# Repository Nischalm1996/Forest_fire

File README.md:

# Forest_fire

## BASE STATION
| NAME     | Pin |
|----------|-----|
| IO0_LORA | D2  |
| RX_GSM   | D3  |
| TX_GSM   | D4  |
| OK       | D5  |
| LEFT     | D6  |
| RIGHT    | D7  |
| BACK     | D8  |
| RST_LORA | D9  |
| SS_LORA  | D10 |
| MOSI     | D11 |
| MISO     | D12 |
| SCK      | D13 |

### MODULES USED
- LORA RA02--d
- GSM SIM 800L--d
- NAVIGATION MODULE --d
- DISPLAY I2C 16*2 --d https://github.com/VaSe7u/LiquidMenu

## NODE_DEVICE
| NAME     | Pin |
|----------|-----|
|   DHT11  | D5  |
| MQ2D0    | D6  |
| PIR      | D7  |
| IO0_LORA | D8  |
| RST_LORA | D9  |
| SS_LORA  | D10 |

### MODULES USED
- MQ2 -- d
- PIR --d
- DHT11-- d
- GPS --d
- LORA RA02 --d

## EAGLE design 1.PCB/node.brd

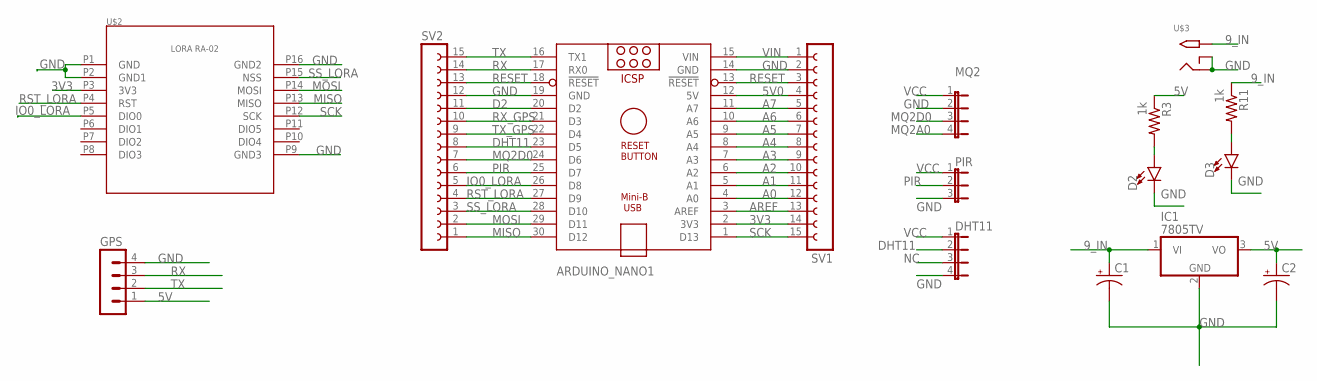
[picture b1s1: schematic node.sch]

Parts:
ARDUINO_NANO1: ARDUINO_NANO
C1, C2: CPOL-USE3.5-8; E3,5-8
D2, D3: LED3MM; LED_3MM
DHT11: JP4E; JP4
GPS: MA04-1
IC1: 7805TV; TO220V
MQ2: JP4E; JP4
PIR: JP2E; JP2
R3, R11: 1k; M0805
SV1, SV2: FE15-1; FE15
U$2: LORA_RA-02; RA-02
U$3: 2.1MMJACKTHM; PJ-102A

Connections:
3V3: ARDUINO_NANO1.2 (3V3), SV1.14, U$2.P3 (3V3)
5V: C2.+, GPS.1, IC1.3 (VO), R3.1
5V0: ARDUINO_NANO1.12 (5V), SV1.4
9_IN: C1.+, IC1.1 (VI), R11.1, U$3.TIP
A0: ARDUINO_NANO1.4 (A0), SV1.12
A1: ARDUINO_NANO1.5 (A1), SV1.11
A2: ARDUINO_NANO1.6 (A2), SV1.10
A3: ARDUINO_NANO1.7 (A3), SV1.9
A4: ARDUINO_NANO1.8 (A4), SV1.8
A5: ARDUINO_NANO1.9 (A5), SV1.7
A6: ARDUINO_NANO1.10 (A6), SV1.6
A7: ARDUINO_NANO1.11 (A7), SV1.5
AREF: ARDUINO_NANO1.3 (AREF), SV1.13
D2: ARDUINO_NANO1.20 (D2), SV2.11
DHT11: ARDUINO_NANO1.23 (D5), DHT11.2, SV2.8
GND: ARDUINO_NANO1.14 (GND), ARDUINO_NANO1.19 (GND), C1.-, C2.-, D2.K (C), D3.K (C), DHT11.4, GPS.4, IC1.2 (GND), MQ2.2, PIR.3, SV1.2, SV2.12, U$2.P1 (GND), U$2.P2 (GND1), U$2.P9 (GND3), U$2.P16 (GND2), U$3.RING, U$3.RING_SW
IO0_LORA: ARDUINO_NANO1.26 (D8), SV2.5, U$2.P5 (DIO0)
MISO: ARDUINO_NANO1.30 (D12), SV2.1, U$2.P13 (MISO)
MOSI: ARDUINO_NANO1.29 (D11), SV2.2, U$2.P14 (MOSI)
MQ2A0: MQ2.4
MQ2D0: ARDUINO_NANO1.24 (D6), MQ2.3, SV2.7
unnamed: D3.A, R11.2
unnamed: D2.A, R3.2
NC: DHT11.3
PIR: ARDUINO_NANO1.25 (D7), PIR.2, SV2.6
RESET: ARDUINO_NANO1.13 (!RESET), ARDUINO_NANO1.18 (!RESET), SV1.3, SV2.13
RST_LORA: ARDUINO_NANO1.27 (D9), SV2.4, U$2.P4 (RST)
RX: ARDUINO_NANO1.17 (RX0), GPS.3, SV2.14
RX_GPS: ARDUINO_NANO1.21 (D3), SV2.10
SCK: ARDUINO_NANO1.1 (D13), SV1.15, U$2.P12 (SCK)
SS_LORA: ARDUINO_NANO1.28 (D10), SV2.3, U$2.P15 (NSS)
TX: ARDUINO_NANO1.16 (TX1), GPS.2, SV2.15
TX_GPS: ARDUINO_NANO1.22 (D4), SV2.9
VCC: DHT11.1, MQ2.1, PIR.1
VIN: ARDUINO_NANO1.15 (VIN), SV1.1

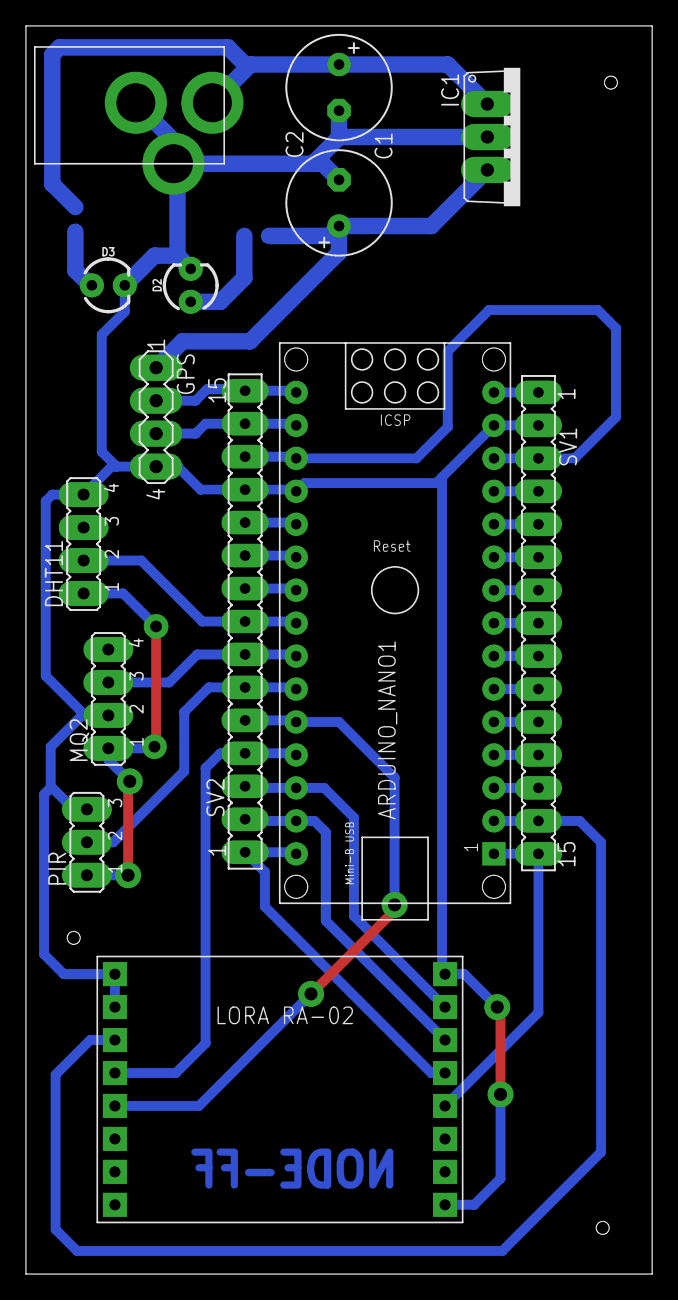
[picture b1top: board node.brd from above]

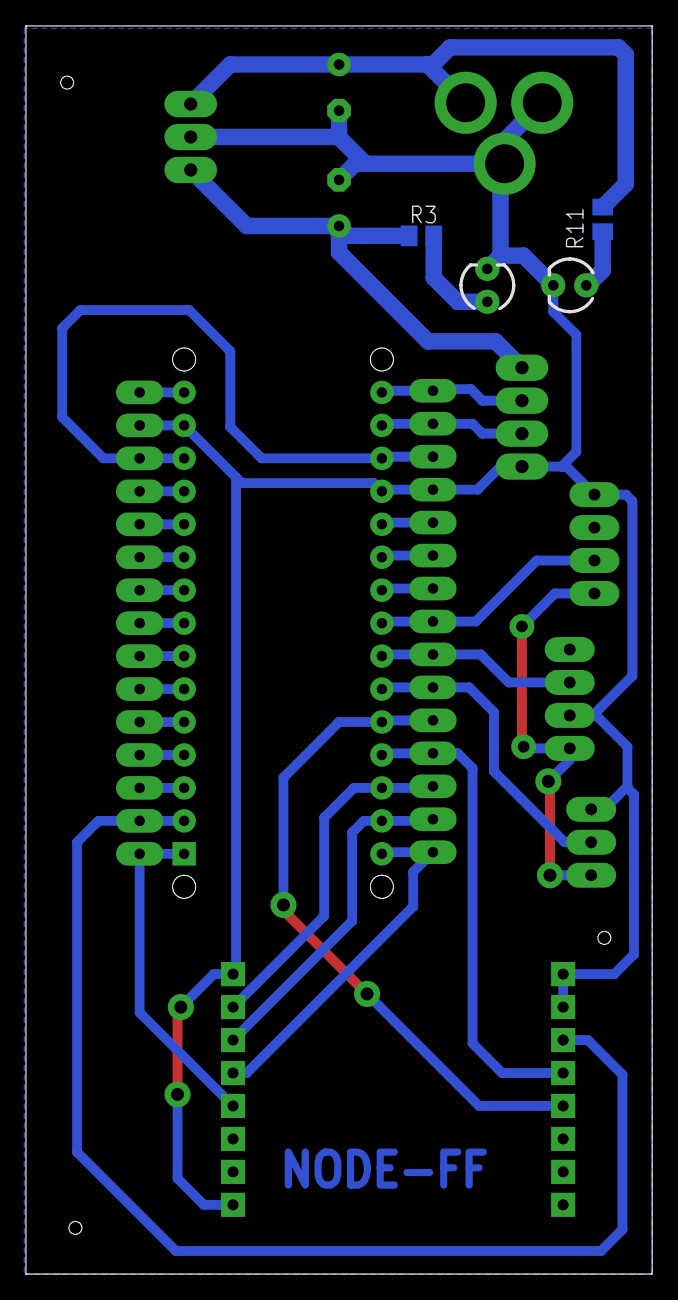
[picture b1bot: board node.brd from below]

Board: 2 copper layers, 48.3 x 96.2 mm, 16 parts (2 on the bottom side), 33 nets.

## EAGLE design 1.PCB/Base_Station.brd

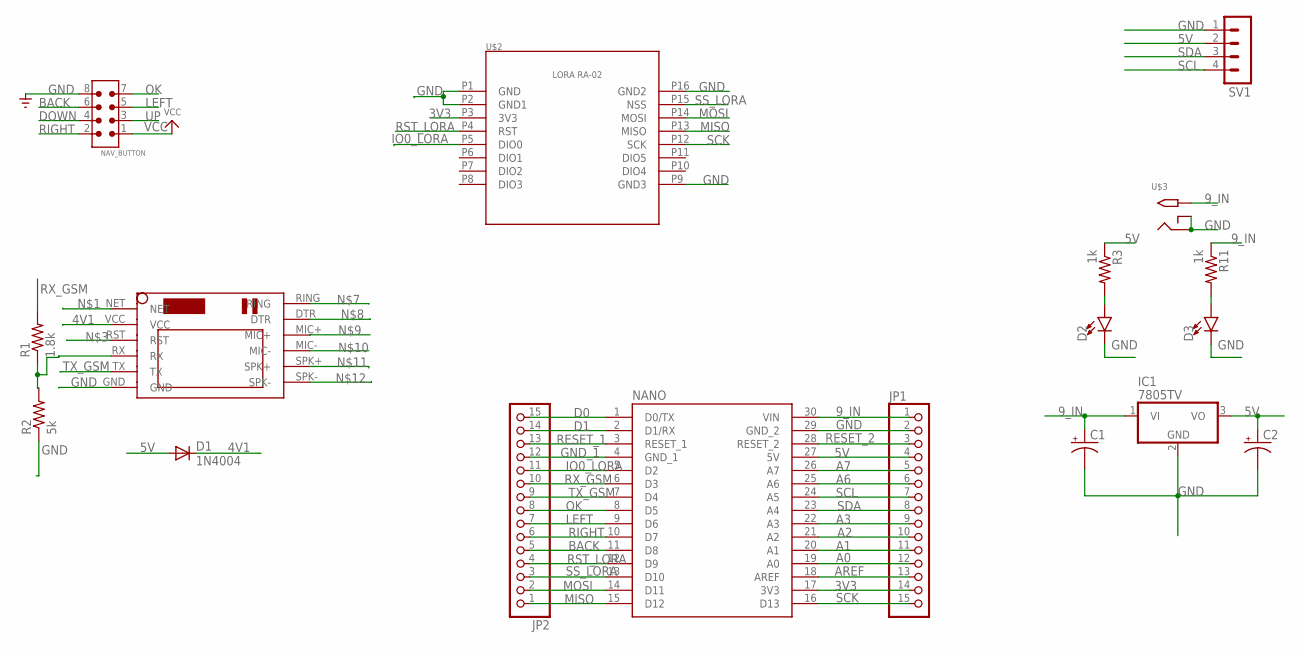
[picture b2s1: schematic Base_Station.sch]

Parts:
C1, C2: CPOL-USE3.5-8; E3,5-8
D1: 1N4004; DO41-10
D2, D3: LED3MM; LED_3MM
IC1: 7805TV; TO220V
JP1, JP2: PINHD-1X15; 1X15
NANO: A000005; MODULE_A000005
NAV_BUTTON: 6120XX21621_61200821621; 61200821621
R1: 1.8k; 0805-THM
R2: 5k; 0805-THM
R3, R11: 1k; M0805
SV1: MA04-1
U$1: SIM800LMODULE
U$2: LORA_RA-02; RA-02
U$3: 2.1MMJACKTHM; PJ-102A

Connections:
3V3: JP1.14, NANO.17 (3V3), U$2.P3 (3V3)
4V1: D1.C, U$1.VCC
5V: C2.+, D1.A, IC1.3 (VO), JP1.4, NANO.27 (5V), R3.1, SV1.2
9_IN: C1.+, IC1.1 (VI), JP1.1, NANO.30 (VIN), R11.1, U$3.TIP
A0: JP1.12, NANO.19 (A0)
A1: JP1.11, NANO.20 (A1)
A2: JP1.10, NANO.21 (A2)
A3: JP1.9, NANO.22 (A3)
A6: JP1.6, NANO.25 (A6)
A7: JP1.5, NANO.26 (A7)
AREF: JP1.13, NANO.18 (AREF)
BACK: JP2.5, NANO.11 (D8), NAV_BUTTON.6
D0: JP2.15, NANO.1 (D0/TX)
D1: JP2.14, NANO.2 (D1/RX)
DOWN: NAV_BUTTON.4
GND: C1.-, C2.-, D2.K (C), D3.K (C), IC1.2 (GND), JP1.2, NANO.29 (GND_2), NAV_BUTTON.8, R2.1, SV1.1, U$1.GND, U$2.P1 (GND), U$2.P2 (GND1), U$2.P9 (GND3), U$2.P16 (GND2), U$3.RING, U$3.RING_SW
GND_1: JP2.12, NANO.4 (GND_1)
IO0_LORA: JP2.11, NANO.5 (D2), U$2.P5 (DIO0)
LEFT: JP2.7, NANO.9 (D6), NAV_BUTTON.5
MISO: JP2.1, NANO.15 (D12), U$2.P13 (MISO)
MOSI: JP2.2, NANO.14 (D11), U$2.P14 (MOSI)
unnamed: D3.A, R11.2
unnamed: R1.1, R2.2, U$1.RX
unnamed: D2.A, R3.2
OK: JP2.8, NANO.8 (D5), NAV_BUTTON.7
RESET_1: JP2.13, NANO.3 (RESET_1)
RESET_2: JP1.3, NANO.28 (RESET_2)
RIGHT: JP2.6, NANO.10 (D7), NAV_BUTTON.2
RST_LORA: JP2.4, NANO.12 (D9), U$2.P4 (RST)
RX_GSM: JP2.10, NANO.6 (D3), R1.2
SCK: JP1.15, NANO.16 (D13), U$2.P12 (SCK)
SCL: JP1.7, NANO.24 (A5), SV1.4
SDA: JP1.8, NANO.23 (A4), SV1.3
SS_LORA: JP2.3, NANO.13 (D10), U$2.P15 (NSS)
TX_GSM: JP2.9, NANO.7 (D4), U$1.TX
UP: NAV_BUTTON.3
VCC: NAV_BUTTON.1

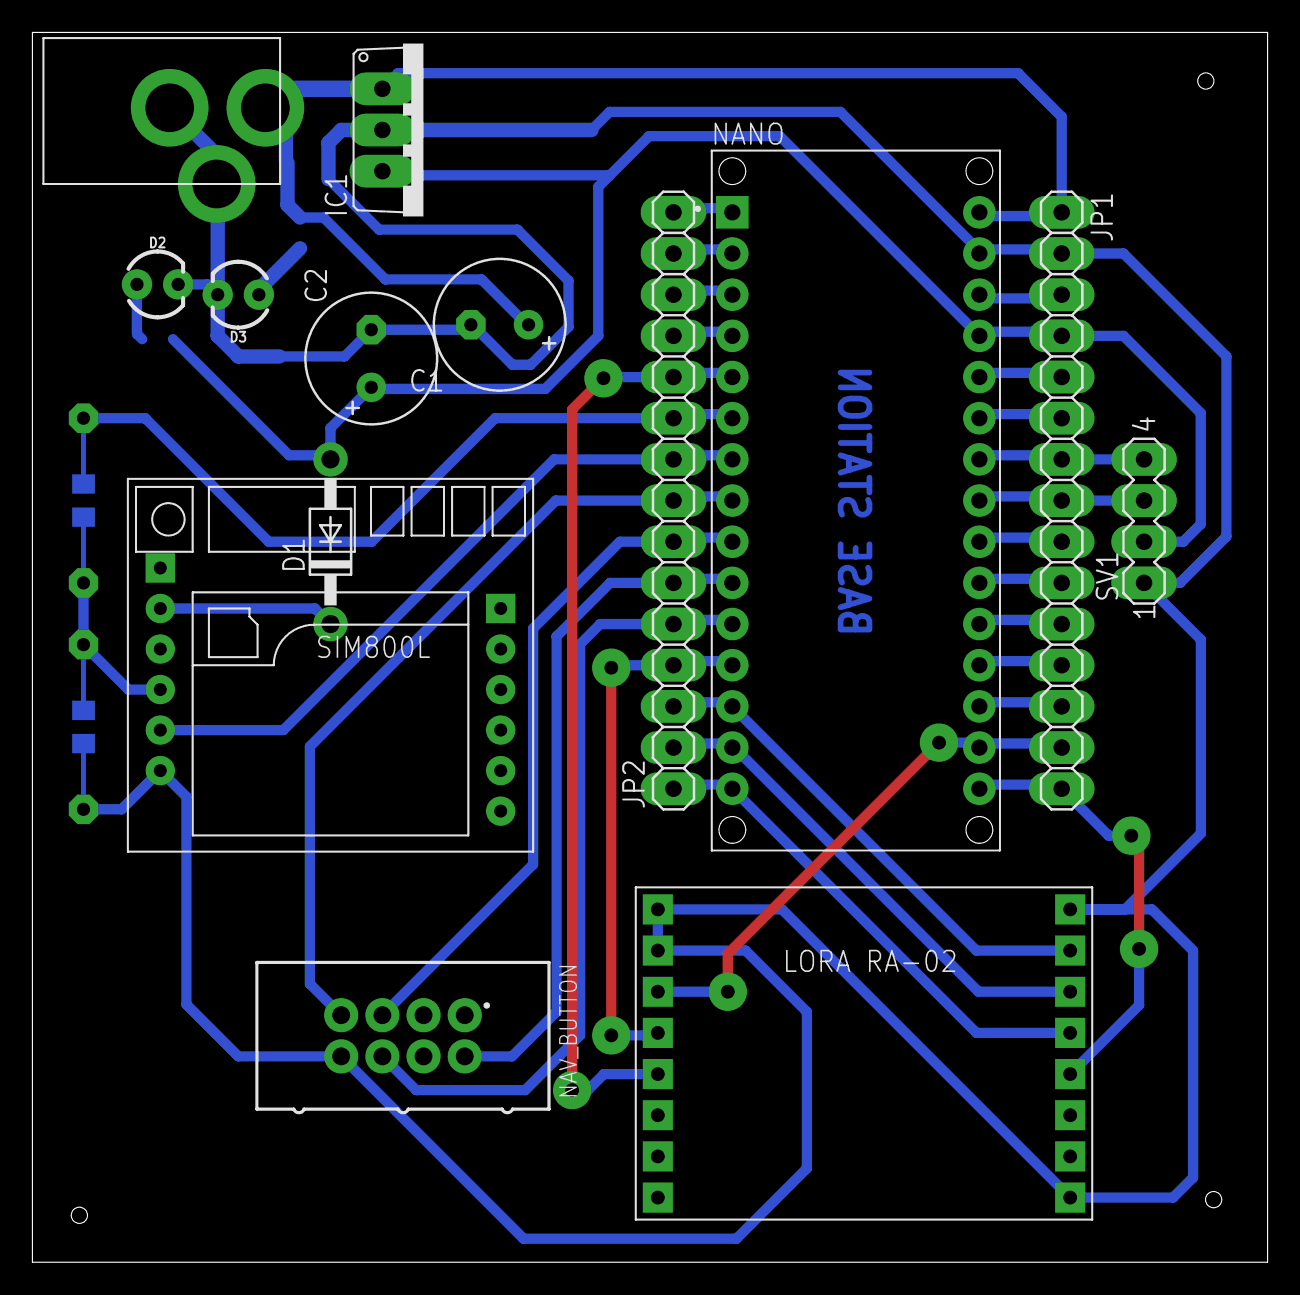
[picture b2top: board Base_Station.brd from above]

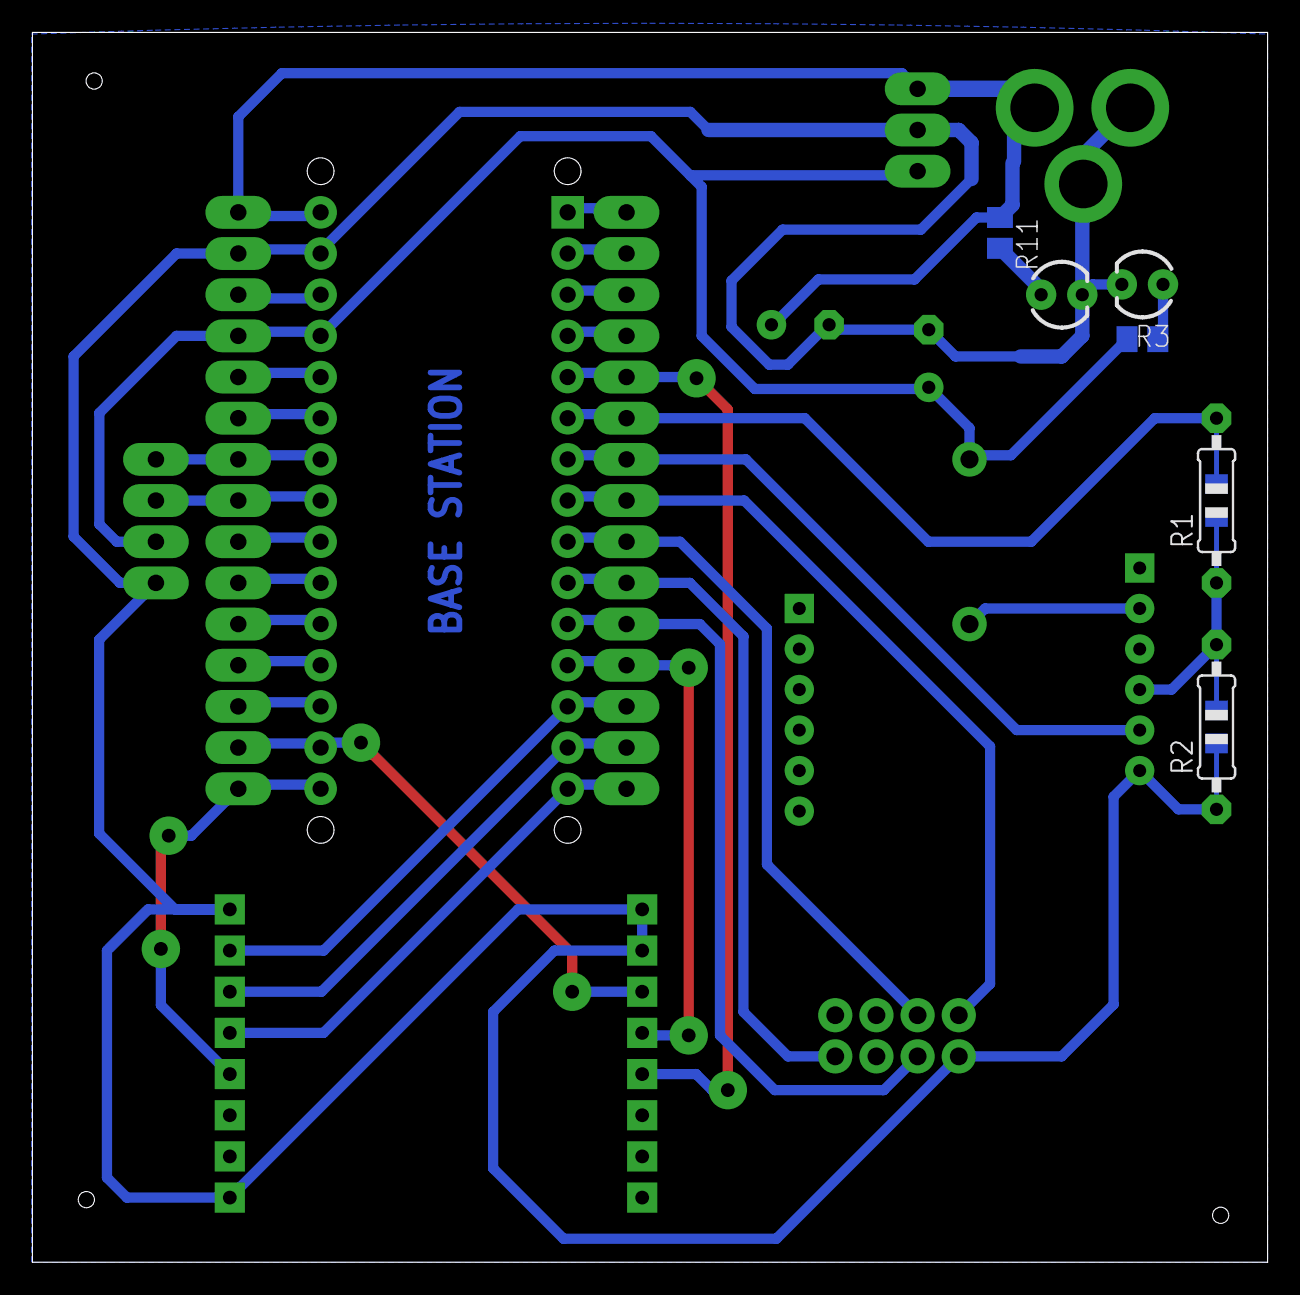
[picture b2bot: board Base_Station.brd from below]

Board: 2 copper layers, 76.2 x 75.9 mm, 18 parts (4 on the bottom side), 34 nets.

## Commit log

2021-02-19 First Commit_project creation
2021-03-16 directory updated
2021-03-16 edited PCB basestation
2021-03-25 MADE CHANGES TO README
2021-04-04 base station edited
2021-04-04 updated node
2021-04-15 updaed node
2021-04-15 added GSM; LORA;
2021-04-15 pushing basic LCD with screens
2021-04-16 ADDED LORA TO NODE
2021-04-16 added schematics
2021-04-16 updated gps
2021-04-16 created pir.h
2021-04-16 added mq2.h
2021-04-16 added dht11
2021-04-16 update platform ini
2021-05-14 forest_fire_node
    kindly check the code and let me know
2021-05-15 working code v0
2021-05-24 basestation
2021-05-26 changes done
2021-05-26 node_arduino added
2021-07-07 temp base station with lora working
2021-07-07 Node device working lora
2021-07-07 gps working
2021-07-20 updated code
2021-07-20 compiled
2021-07-20 debugged
2021-07-26 added for nodes
2021-07-29 complete code

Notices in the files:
parts and their libraries:
Wurth_Connectors_WR-BHD: Copyright: Würth Elektronik
SparkFun-LED: Licensing: Creative Commons ShareAlike 4.0 International - https://creativecommons.org/licenses/by-sa/4.0
